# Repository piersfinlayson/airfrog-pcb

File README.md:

# airfrog-pcb

Airfrog is a tiny WiFi co-processor for microcontrollers, adding wireless networking, programming and management.

Amongst other devices, Airfrog supports [One ROM](https://onerom.org).

| Mini (ESP32-C3) | Pro (ESP32-S3) |
| :---: | :---: |
|  |  |

<em>Currently untested - order at your own risk.</em>

## Files

Download the fab files, KiCad project and schematic PDF for each version from [Releases](../../releases) or generate them with `scripts/generate.sh`.

## Ordering

To have JLCPCB make and assemble the Mini, upload the gerbers `airfrog-mini-gerbers.zip` and choose:

- HASL or ENIG finish
- 4 layers, 1.6 mm thick
- layer stackup JLC04161H-7628
- PCB assembly
- your choice of solder mask colour (the official Airfrog board colour is blue)

Then upload a BOM and CPL:

- top side only soldering socket J1 by hand: `airfrog-mini-bom.csv` and `airfrog-mini-cpl.csv`
- both sides, with J1 fitted by JLCPCB: `airfrog-mini-socket-bom.csv` and `airfrog-mini-socket-cpl.csv`

Check the parts' positions in JLCPCB's preview before you place the order.

For the Pro replace `mini` with `pro` in the filenames.

## Design

Schematics:

- [Mini (PDF)](../../releases/latest/download/airfrog-mini-schematic.pdf)
- [Pro (PDF)](../../releases/latest/download/airfrog-pro-schematic.pdf)

## Developing

The schematics and fab files are generated from scripts. The PCBs are routed by hand in KiCad.

To modify or extend this design start with [DEVELOPMENT.md](DEVELOPMENT.md).

## License

(c) 2026 piers.rocks.

Licensed under the [CERN Open Hardware Licence Version 2 - Weakly Reciprocal](LICENSE) (CERN-OHL-W-2.0).

Boards made from this design must display piers.rocks, as set out in [NOTICE](NOTICE).

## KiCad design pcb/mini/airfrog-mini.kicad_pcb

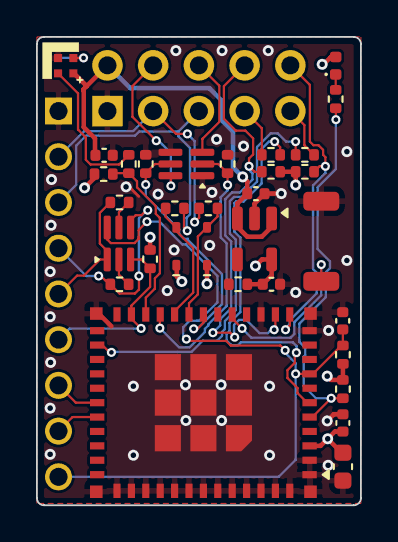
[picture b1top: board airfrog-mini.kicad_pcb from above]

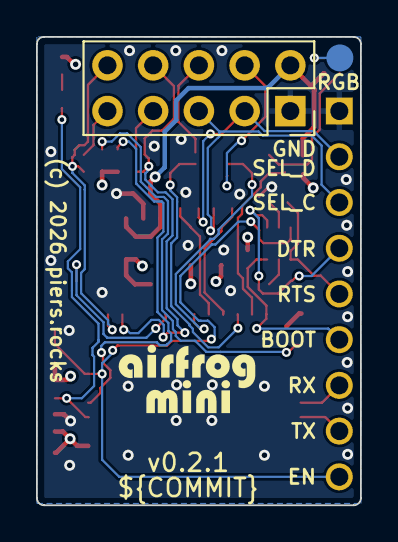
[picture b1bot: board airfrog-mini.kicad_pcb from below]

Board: 4 copper layers, 18.0 x 26.0 mm, 35 parts (2 on the bottom side), 31 nets.

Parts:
C1: 1uF; C_0402_1005Metric
C2, C3: 4.7uF; C_0402_1005Metric
C4, C6: 0.1uF; C_0402_1005Metric
C5: 10uF; C_0603_1608Metric
D1, D2: BAT54WS; D_SOD-323
D3: Blue; LED_0402_1005Metric
D4: RGB; XL-1010RGBC-2812B
J1: One ROM; PinSocket_2x05_P2.54mm_Vertical
J2: User/serial; PinHeader_1x09_P2.54mm_Vertical
Q1: 2N7002DW; SOT-363_SC-70-6
Q2: MMDT3904; SOT-363_SC-70-6
R1, R2, R3, R4, R9, R10, R11, R12: 10K; R_0402_1005Metric
R5, R6, R13: 2K2; R_0402_1005Metric
R7, R8: 4K7; R_0402_1005Metric
R14: 330R; R_0402_1005Metric
R15, R17, R18: 1K; R_0402_1005Metric
SW1: Recovery; SW_SPST_TS-1088-xR020
TP1: DOUT; TestPoint_Pad_D1.5mm
U1: ESP32-C3-MINI-1; ESP32-C6-MINI-1
U2: AP2112K-3.3; SOT-23-5

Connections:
+3V3: C3.1, C4.1, C5.1, D1.1 (K), D2.1 (K), D3.2 (A), R1.1, R2.1, R7.1, R8.1, R11.1, R12.1, R13.1, U1.3 (3V3), U2.5 (VOUT)
+5V: C2.1, C6.1, D4.2 (VDD), J1.2, U2.1 (VIN), U2.3 (EN)
BOOT: J2.6, Q2.3 (C2), R2.2, U1.23 (IO9_BOOT)
BOOTSEL: J1.6, Q1.3 (D)
BOOTSEL_DRV: Q1.5 (G), R4.1, U1.18 (IO4_MTMS)
DTR: J2.4, Q2.4 (E2), R9.1
EN: C1.1, J2.9, Q2.6 (C1), R1.2, U1.8 (EN)
GND: C1.2, C2.2, C3.2, C4.2, C5.2, C6.2, D4.3 (GND), J1.1, J2.1, Q1.1 (S), Q1.4 (S), R3.2, R4.2, R13.2, SW1.2, U1.1 (GND), U1.2 (GND), U1.11 (GND), U1.14 (GND), U1.36 (GND), U1.37 (GND), U1.38 (GND), U1.39 (GND), U1.40 (GND), U1.41 (GND), U1.42 (GND), U1.43 (GND), U1.44 (GND), U1.45 (GND), U1.46 (GND), U1.47 (GND), U1.48 (GND), U1.49 (GND), U1.50 (GND), U1.51 (GND), U1.52 (GND), U1.53 (GND), U2.2 (GND)
J1_7: R17.1, U1.6 (IO3)
J1_9: R18.1, U1.26 (IO18_D-)
LED: R11.2, R14.2, U1.5 (IO2_PU)
unnamed: D3.1 (K), R14.1
unnamed: D4.4 (DIN), R15.2
unnamed: D4.1 (DOUT), TP1.1
unnamed: J1.7, R17.2
unnamed: J1.9, R18.2
unnamed: Q2.2 (B1), R9.2
unnamed: Q2.5 (B2), R10.2
RECOVERY: SW1.1, U1.16 (IO10)
RGB: R12.2, R15.1, U1.22 (IO8_JTD_BOOT)
RTS: J2.5, Q2.1 (E1), R10.1
RUN: J1.4, Q1.6 (D)
RUN_DRV: Q1.2 (G), R3.1, U1.21 (IO7_MTD0)
RXD0: J2.7, U1.30 (IO20_RXD0)
SEL_A: J1.10, R7.2, U1.12 (IO0)
SEL_B: J1.8, R8.2, U1.13 (IO1)
SWCLK: J1.5, J2.3, R5.1
SWCLK_ESP: D1.2 (A), R5.2, U1.20 (IO6_MTCK)
SWDIO: J1.3, J2.2, R6.1
SWDIO_ESP: D2.2 (A), R6.2, U1.19 (IO5_MTDI)
TXD0: J2.8, U1.31 (IO21_TXD0)

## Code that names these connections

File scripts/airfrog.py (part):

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# value -> second-source LCSC part, written to the LCSC alt field
ALTS = {}

# Each variant's module and the module pin of each signal. RUN_DRV and BOOTSEL_DRV are on pins with no pull-up
# and no high glitch at power-up, so the MOSFETs stay off until the firmware drives them. The One ROM signals are
# on the module edge that faces the header on the PCB.
VARIANTS = {
    'mini': {
        'lib_id': LIB + ':ESP32-C3-MINI-1', 'value': 'ESP32-C3-MINI-1',
        'props': {'LCSC': 'C41349510', 'LCSC alt': 'C2838502', 'Comment': 'Espressif ESP32-C3-MINI-1-H4X'},
        'pins': {'EN': 8, 'BOOT': 23, 'TXD0': 31, 'RXD0': 30, 'RUN_DRV': 21, 'BOOTSEL_DRV': 18,
                 'SWCLK_ESP': 20, 'SWDIO_ESP': 19, 'SEL_A': 12, 'SEL_B': 13, 'RECOVERY': 16, 'LED': 5, 'RGB': 22,
                 'J1_7': 6, 'J1_9': 26},
        'nc': [27],
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    'pro': {
        'lib_id': 'RF_Module:ESP32-S3-MINI-1', 'value': 'ESP32-S3-MINI-1',
        'props': {'LCSC': 'C3013941', 'Comment': 'Espressif ESP32-S3-MINI-1-N4R2'},
        'pins': {'EN': 45, 'BOOT': 4, 'TXD0': 39, 'RXD0': 40, 'RUN_DRV': 25, 'BOOTSEL_DRV': 20,
                 'SWCLK_ESP': 19, 'SWDIO_ESP': 21, 'SEL_A': 17, 'SEL_B': 18, 'RECOVERY': 16, 'LED': 15, 'RGB': 30,
                 'J1_7': 27, 'J1_9': 22},
        'nc': list(range(5, 15)) + [23, 24, 26, 28, 29] + list(range(31, 39)) + [41, 44],
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    # J1 is on the underside, so its odd pins are on row 2, the row further from One ROM's edge
    s.pin_power(j, 2, '+5V', length=U)
    s.pin_power(j, 1, 'GND', length=U)
    for pin, net in ((3, 'SWDIO'), (4, 'RUN'), (5, 'SWCLK'), (6, 'BOOTSEL'), (8, 'SEL_B'), (10, 'SEL_A')):
        s.pin_label(j, pin, net)
    # J1-7 and J1-9 are GND on One ROM, so 1K limits the current if the ESP32 drives one high there
    # the resistors are staggered so their labels clear each other and SWCLK
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              fields=fields_at((ox + 6.5, oy + 4.5), (ox + 6.5, oy + 13.5), just='right'),
              props={'Footprint': 'Connector_PinHeader_2.54mm:PinHeader_1x09_P2.54mm_Vertical'})
    s.pin_power(j, 1, 'GND', length=U)
    for pin, net in ((2, 'SWDIO'), (3, 'SWCLK'), (4, 'DTR'), (5, 'RTS'), (6, 'BOOT'), (7, 'RXD0'), (8, 'TXD0'),
                     (9, 'EN')):
        s.pin_label(j, pin, net)
    s.text('SEL_D', P(ox + 16, oy + 6))
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    W((cx - 3, cy), (cx - 4, cy))
    passive('R15', '1K', cx - 5, cy, rot=90, fields='below1')
    W((cx - 6, cy), (cx - 8, cy))
    s.label('RGB', P(cx - 8, cy), 180)
    W((cx + 3, cy), (cx + 8, cy))
    s.add('Connector:TestPoint', 'TP1', 'DOUT', P(cx + 8, cy), in_bom=False,
          props={'Footprint': 'TestPoint:TestPoint_Pad_D1.5mm'},
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               fields={'Reference': (P(ox + 19.6, oy + 4)[0], P(ox + 19.6, oy + 4)[1], 'right', 'center', False),
                       'Value': (P(ox + 20.4, oy + 4)[0], P(ox + 20.4, oy + 4)[1], 'left', 'center', False)})
    W((ox + 18, oy + 6), (ox + 14, oy + 6))
    s.label('RECOVERY', P(ox + 14, oy + 6), 180)
    W((ox + 22, oy + 6), (ox + 24, oy + 6))
    s.power('GND', P(ox + 24, oy + 6))

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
